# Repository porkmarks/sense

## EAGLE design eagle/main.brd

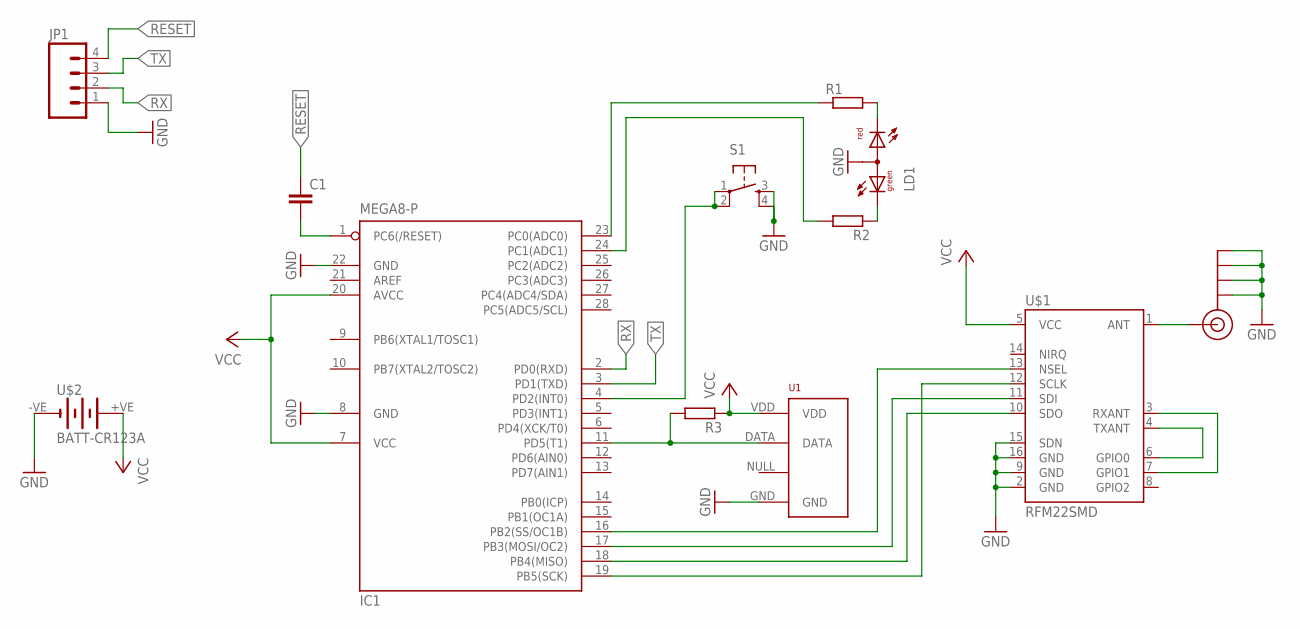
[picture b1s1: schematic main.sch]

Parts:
C1: C-EU050-025X075; C050-025X075
IC1: MEGA8-P; DIL28-3
J$2: SMA_EDGE; SMA-EDGE
JP1: M04PTH; 1X04
LD1: DUOLED-RG-A; DUOLED-A-5MM
R1, R2, R3: R-EU_0204/5; 0204/5
S1: TAC_SWITCHPTH; TACTILE-PTH
U1: RHT03_DHT-22_AM2302RA; RHT03_DHT-22/RA
U$1: RFM22SMD; RFM22-XXX-S2
U$2: BATT-CR123A; KEYSTONE-2/3A

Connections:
GND: IC1.8 (GND), IC1.22 (GND), J$2.GND@0 (GND), J$2.GND@1 (GND), J$2.GND@2 (GND), J$2.GND@3 (GND), JP1.1, LD1.A, S1.3, S1.4, U1.GND, U$1.2 (GND), U$1.9 (GND), U$1.15 (SDN), U$1.16 (GND), U$2.-VE (-)
unnamed: IC1.16 (PB2(SS/OC1B)), U$1.13 (NSEL)
unnamed: IC1.17 (PB3(MOSI/OC2)), U$1.11 (SDI)
unnamed: IC1.18 (PB4(MISO)), U$1.10 (SDO)
unnamed: IC1.19 (PB5(SCK)), U$1.12 (SCLK)
unnamed: U$1.4 (TXANT), U$1.6 (GPIO0)
unnamed: U$1.3 (RXANT), U$1.7 (GPIO1)
unnamed: J$2.SIG (SIGNAL), U$1.1 (ANT)
unnamed: LD1.CR, R1.2
unnamed: LD1.CX (CG), R2.1
unnamed: IC1.23 (PC0(ADC0)), R1.1
unnamed: IC1.24 (PC1(ADC1)), R2.2
unnamed: IC1.11 (PD5(T1)), R3.2, U1.DATA
unnamed: C1.2, IC1.1 (PC6(/RESET))
unnamed: IC1.4 (PD2(INT0)), S1.1, S1.2
RESET: C1.1, JP1.4
RX: IC1.2 (PD0(RXD)), JP1.2
TX: IC1.3 (PD1(TXD)), JP1.3
VCC: IC1.7 (VCC), IC1.20 (AVCC), R3.1, U1.VDD, U$1.5 (VCC), U$2.+VE (+)

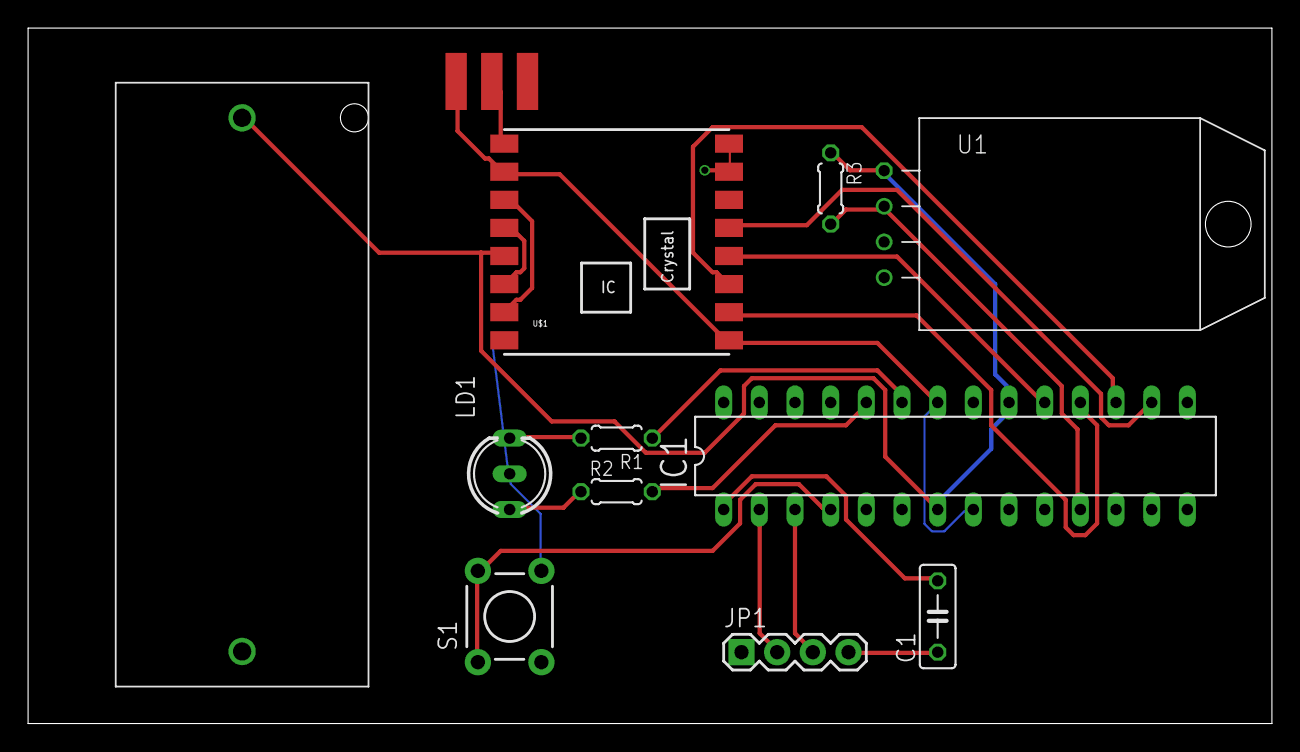
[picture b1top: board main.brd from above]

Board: 2 copper layers, 88.6 x 49.5 mm, 12 parts (0 on the bottom side), 19 nets.

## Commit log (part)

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2015-09-21 displaying multiple lines for multiple files
2015-09-22 Added voltage reading Added comms class that handles the comm protocol Added fade in/out for leds Wake up from sleep on interrupt
2015-09-22 Sharing code Comms done, messages work
2015-09-22 Added a stl implementation
2015-09-22 started sensor management
2015-09-22 added sensor data
2015-09-23 Added eagle files
2015-09-28 labels and checkboxes
2015-10-04 arranged the divs in the page, associated checkboxes with the graphs
2015-10-07 humidity valueline
2015-10-09 Changed the month 2 separate axis working
2015-10-19 buttons for each period
2015-10-26 Ignoring the reply message
2015-10-26 Removed unneeded files
2015-11-04 ! removed files
2015-11-26 refactored the code graph width resizes on page resize
2015-12-09 Ignoring files Storage is now common Added unit tests for storage
2015-12-09 more ignores
2015-12-09 more storage tests removed some avr warnings
2015-12-12 Added sensor management Added comms scheduler Added fifo and command parser
2015-12-15 combined scheduler & sensors merged all measurements in one vector
2015-12-20 Moved server to base
2015-12-21 Optimized reading and reduced memory by 320 bytes
2015-12-21 Logging fixes and renamed server by base
2015-12-23 Better timekeeping with a chrono-like utility
2015-12-24 alarms page almost functional- drop down list needs php
2016-03-15 - changed the graphics - login system with user authentification
2016-05-16 -fixed absolute addresses -started overview page
2016-05-19 Fixed sensor handshake
2016-05-19 attempted to connect the sensors_database to a sensorsettings page
2016-05-20 Fixes
2016-05-25 Fixed the updateSensorSettings Fixed the connection to the database
2016-05-26 ignoring files
2016-05-26 Reorganized files
2016-05-26 Reorganized some pages Added basic overview
2016-05-26 error check
2016-05-27 test
2016-05-28 Better radio config Fixed measurement index gaps
2016-05-30 Started support for multiple configs
2016-05-31 Fixed multi-config tracking
2016-10-23 Added Admin class to handle configuration and communication with the Admin app
2016-11-09 CSS problems resolved
2016-12-15 added support for SHT2x temp/humidity sensors
2016-12-15 added support for sht2x temp sensors
2016-12-15 added support for sht21 sensors fixed the time drift bug by working with relative times instead of absolutes
2016-12-15 sht21
2017-03-12 Split the DBs into system and user Optimized sensor memory
2017-03-12 moved everything to the main git ignore
2017-04-01 creating the default table structure
2017-04-01 Moved the configs from the system to the user db
2017-04-14 Removed strings in a desperate attempt to gain some memory on the avr
2017-04-14 Allowing batch measurement reporting Using a condition variable for the worker thread instead of sleeping
2017-04-14 Fixed measurement_index bug when sending >1 batches
2017-04-14 Cleaned up debug strings
2017-06-25 Added server functionality, removed the DB
2017-06-26 Added more commands
2017-06-26 Initial version of the manager
2017-06-26 nicer ui
2017-06-27 Config & Measurements pages
2017-06-28 Started the DB and measurements widget
2017-06-29 More icons Working measurements filter Started the plot
2017-06-29 Added sensor model Finished filters Started alarms
2017-06-30 Bind sensor fixes
2017-06-30 adding alarms
2017-06-30 More UI work Alarms working
2017-06-30 Polished alarms
2017-07-01 various fixes
2017-07-01 Prepared for the saving thread
2017-07-01 saving the DB
2017-07-01 saving & loading dbs
2017-07-01 Optimized the models a lot by caching the icons
2017-07-02 small clarification
2017-07-02 Comms with base station working Alarms support sensor filtering now Sorting for measurements
2017-07-02 alarms are not global anymore Reorganized the data a bit in the DB
2017-07-02 Added proper and simpler delegates
2017-07-02 Exporting done
2017-07-03 Added measurement id Started report generation Added battery estimator excel
2017-07-03 Added export dialog Added export preview Added configure alarm dialog
2017-07-03 Visual fix
2017-07-06 Added plot widget legend and tool tips
2017-07-07 Filter for smoothing graphs
2017-07-08 Added reports
2017-07-09 ftp username & pass encryption support
2017-07-10 Started email functionality
2017-07-12 Added emailer class
2017-07-12 Emailing almost done
2017-07-12 Emails working
2017-07-13 Automated reports
2017-07-14 Deleting sensors, alarms and reports
2017-07-15 Improved comms Fixed negative timestamp bug
2017-07-15 Saving the dbs in the program folder
2017-07-16 Fixed backup problems
2017-07-16 Fixed BS name
2017-07-18 Compile warning
2017-07-18 Added calibration support
2017-07-20 string key and stable hashing for passwords
2017-07-22 new UI
2017-07-22 More feedback
2017-07-23 Added S/N for sensors Added logging
2017-07-24 Fix some logs
2017-07-31 Fixed windows stuff
2017-07-31 Added custom range for the plot
2017-08-02 Multiple recipients Latest feedback applied
2017-08-03 Feedback #2: Fixed BS discovery Users are now case insensitive Fixed utf8 symbols in CSV
2017-08-05 Feedback #2
2017-08-05 Removed uneeded file
2017-08-05 Removed the fixed animation as it's redundant now
2017-08-10 Fixed PNG export quality
2017-08-12 added helper sketches
2017-08-12 started FTP
2017-08-15 Faster timestamp sorting
2017-08-15 Better email testing dialog More sensor flashing info
2017-10-17 Performance improvements
2017-10-18 Fixed email
2017-10-18 Removed sensor errors column
2017-10-21 Editing sensors Data filters
2017-10-29 Saving column sizes Fixed crash in the plot widget Disconnecting from the connections before reconnecting again on init Fixed changing IP address of the base station
2017-10-29 Attempt to fix the save crash
2017-10-29 Added missing icons including an app icon
2017-10-29 converted stream outs to logs
2017-10-30 Arduino ide compat
2017-11-26 attempt to fix crash
2017-11-26 flushing the buffer when writing the stack trace
2017-11-26 added missing include folders
2017-11-26 moved files around
2017-11-26 new settings for the sensor
2017-11-26 Fixed project
2017-11-26 not ignoring makefiles anylonger
2017-11-26 removed temp file
2017-11-26 Compilation fixes
2017-11-26 missing define
2017-11-26 missing include
2017-11-26 Added detailed sensor report
2017-11-26 fixed missing definition
2017-11-26 Fixed some responses
2017-11-26 fixed serialization issue
2017-11-26 Added average signal strength Fixed some sensor bugs
2017-12-27 improved comms
2017-12-27 Added working makefile
2018-04-26 More files ignored
2018-04-26 Comp9ile fixes
2018-08-11 Fixed BS names
2018-08-17 Fixed crash when deleting
2018-08-17 Fixed computed comms period
2018-08-17 Fixed selected sensors initial value Don't show plot labels for unselected sensors
2018-08-17 Fixed next comms slot display and calculation Fixed connect/reconnect from BS
2018-09-05 Fixed Config handling Added logs
2018-09-05 Fixed compilation error on windows (high res clock doesnt have to_clock_t)
2018-09-05 Fixed crash when not connected to a db
2018-09-11 Fixed sensor filter for reports Fixed refreshing date/time filter after a day Fixed a lot of warnings
2018-09-11 Switched from QtCharts to QCustomPlot
2018-09-15 Optimized log loading/saving Fixed some small leaks
2018-09-17 Faster plot drawing / annotations Fixed unreadable colors
2018-10-10 Added file for log error
2018-10-10 Allow measurements to be confirmed before sending the config
2018-10-10 MQTT icon
2018-10-10 Select All / Select None buttons
2018-10-10 Batch measurement reporting to reduce the amount of data written in the DB
2018-10-10 Faster measurement refresh
2018-10-10 Version increase
2018-10-10 mqtt icon added
2018-10-11 File format for the logs Less memory usage due to logs
2018-10-12 Fixed plot slowdown after many refreshes
2018-10-12 Empty method
2018-10-12 Transmission power method
2018-10-12 Removed unused files
2018-10-14 Version increase Fixed warning
2018-11-04 Updated sensor info New fuses
2018-11-08 Replaced rfm with lora
2018-11-18 Lora comms Not using arduino any longer
2018-11-18 Error reporting
2018-11-18 Power changes
2018-11-23 Added timeouts for disconnection Fixed crash in the socket adapter
2018-11-24 Very robust comms New simplified sleeping model
2018-11-25 Increased timeouts
2018-11-25 Fixed the yellow led Added some reserved space in the data defs Fixed the i2c bus (hopefully)
2018-11-29 Fixed the sensor instability Added error reporting Added sensor details dialog (not yet linked)
2018-11-29 Fixed crash Simplified logs
2018-11-30 Fixed bug causing sensors to stop measuring
2018-12-09 Formatting fixes Focus issue fixed
2018-12-11 Styling fixes
2018-12-14 Added About dialog Reorganized the settings screen Fixed the tab order for all widgets Added logout and exit menus
2018-12-27 Fixed milliseconds display
2018-12-27 Fixed the yellow led
2018-12-27 Added background battery easurements
2018-12-27 Added RT measurements when requesting the configs
2018-12-27 Battery and comms fixes
2018-12-27 Started base station relay support
2018-12-27 Super solid comms Pairing on another frequency
2018-12-27 Deleted unused stuff
2018-12-27 Removed sensors tests
2018-12-27 Compile fix
2018-12-27 Fixed compilation on the raspberry pi
2018-12-27 Dialog settings fixes
2018-12-29 Threaded radio comms Better handling of timeouts
2018-12-29 Fixed pairing
2018-12-29 Hiding stored measurements if below 10
2018-12-29 More error messages
2019-01-25 fixed out of phase messages
2019-01-27 1.0.14
2019-02-02 Fixed emails
2019-02-02 Fixed the makefile
2019-04-09 Fixed for future measurements
2019-12-22 Added local crc
2019-12-22 moved to base/src
2019-12-27 Trying to increase battery life Split the battery buard into radio and sensor, with different min voltages Turning off more peripherals
2019-12-27 Added cereal for serialization
2019-12-27 Compiling with vs 2019
2019-12-28 Changed icon set Fixed bad signal after pairing Fixed reverting to normal state after pairing Better battery estimation
2019-12-28 Fixed revert to normal state
2019-12-28 Fixed b2s signal reporting
2019-12-28 Showing both S2B and B2S signals in sensor details ErrorCounters clearing
2019-12-29 Maximized resolution for temp and humidity Persistent plots
2019-12-30 Rounding
2020-01-03 Removed cereal and rapidjson
2020-01-04 Low/High alerts for temp and hum
2020-01-06 Added soft/hard thresholds for alarms Added configurable battery and signal thresholds
2020-01-06 Email alerts
2020-01-06 Fixed first-time bs discovery Fixed email alert colors
2020-01-07 Removed radio Acks Fixed first time config being broken Added sensor settings permission
2020-01-10 Removed the settings class and collapsed it in the DB Eliminated potential data loss on crash Saving data only when changed
2020-01-13 Added protocol version to be able to upgrade sensors over the air
2020-01-13 Csv settings working (both in settings and edport overrides)
2020-01-15 Reports with csv attachment working
2020-01-17 Threaded comms to reduce the chance of sensor blackout due to UI being slow Fixed alarm email colors Added alarm triggers in plots Fixed plot averaging
2020-01-18 Finished retries Added more sensor stats
2020-01-19 Started tests
2020-01-19 Moved tests around
2020-01-19 Added more tests Added DB clock override for tests
2020-01-19 Fixed clock config
2020-01-20 Cosmetic fixes
2020-01-20 More tests
2020-01-20 Much faster measurements model Added sorting in the DB filter
2020-01-21 More sensor tests
2020-01-21 Reorganized tests
2020-01-22 Fixed error
2020-01-25 Fixed alarms Added hysteresis in the battery/signal alarms
2020-01-26 Fixed timeout issue
2020-02-09 Fixed a plot crash Fixed random pixels i nthe miniplot Changed the binding dialog
2020-08-31 Fixed a few bugs
2020-09-05 New storage for big memory
2020-09-08 new storage working
2020-11-09 Performance improvements Backing store unit tests

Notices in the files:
parts and their libraries:
SparkFun-Connectors: Licensing: Creative Commons ShareAlike 4.0 International - https://creativecommons.org/licenses/by-sa/4.0
eagle-library-edeca.net-v5: This is v1 and is licensed under the Creative Commons (Attribution-Non-Commercial-Share Alike 2.0 UK)
